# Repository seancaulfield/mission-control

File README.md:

# Mission Control: RAVE EDITION
### A nearly complete internal replacement for the IBM Model M122: Now with RGB!!

This project is designed to replace all internal compoents of an Model M122 keyboard, and is based off my previous [Mod Mmm Project](https://github.com/dcpedit/mod-mmm).  Only the curved steel backplate is needed for the PCB to be mounted on.

Image gallery: https://imgur.com/a/wuXMWVg

## Features

* Per-key RGB support
* High current 5V path (because we're going to be pulling a LOT of current...)
* FR4 plate files as alternative
* Hotswap sockets for MX switches
* Multiple layout support, including ISO, split spacebar, and 4x5 macropad for numpad. [KLE link](http://www.keyboard-layout-editor.com/#/gists/d71adbbb0de71b98bfe3e79a4a607b5c)
* PCB mount stabilizers
* Solenoid
* LCD display
* USB-C support
* Bluetooth support (via PillBug)
* QMK/VIA firmware
* ZMK firmware (for BT PillBug)

## The Build "Stack"

The following is a table of measurements of everything that's stacked on top of the steel backplate.  The key spacing was taken from hires scans I made of the Model M's wiring membrane.  I recalculated the spacing for each decrease in radius except for the foam where I reused the numbers from the switch plate.  I was lazy and figured foam can stretch anyways.

| Part            | Thickness (mm) | Radius (mm) | Radius Start | 1u vertical spacing (mm) |
|-----------------|----------------|-------------|--------------|--------------------------|
| Steel backplate | 1.0            | 276.635     | inner        | 20.617
| Hex Standoffs   | 4.0            | n/a         | n/a          | n/a
| PCB     | 1.0            | 272.135     | center       | 20.560
| Plate Foam      | 3.5            | n/a         | n/a          | n/a
| Switch Plate    | 1.5            | 267.385     | center       | 20.201

## Parts List

| Part                        | Count | Notes |
|-----------------------------|-------|-------|
| Mission Control PCB         | 1     | 1mm FR4 thickness
| Blackpill (STM32F411)       | 1     |
| M2.5x3mm Wafer Screw        | 138   | [Link](https://www.aliexpress.us/item/2255800885711092.html?spm=a2g0o.order_list.order_list_main.22.1875180223MOsy&gatewayAdapt=glo2usa&_randl_shipto=US)
| M2.5x4mm Hex Standoff       | 69    | [Link](https://www.aliexpress.us/item/2251832790997097.html?spm=a2g0o.order_list.order_list_main.23.1875180223MOsy&gatewayAdapt=glo2usa&_randl_shipto=US)
| BAV70 Diodoe                | 64    | [Link](https://www.mouser.com/ProductDetail/Nexperia/BAV70215?qs=me8TqzrmIYX%252B%2FJ6jIjzNeA%3D%3D&countrycode=US&currencycode=USD)
| Piezo Buzzer                | 1     | [Link](https://www.digikey.com/en/products/detail/tdk-corporation/PS1240P02BT/935924)
| 5v Solenoid                 | 1     | [Link](https://www.digikey.com/en/products/detail/sparkfun-electronics/ROB-11015/6163694)
| Hotswap Sockets       | 108 - 115 | Recommend Gateron v2
| 2mm LED                     | 2     | For switch status led. [Link](https://www.amazon.com/gp/product/B01C5HL0PO/ref=ppx_yo_dt_b_search_asin_title?ie=UTF8&th=1)
| 10kΩ Resistor               | 2     | For keycap LED. Smaller = brighter |
| 22kΩ Resistor               | 1     | Pullup for pin A10 |
| TIP120 Transistor           | 1     | For solenoid. [Link](https://www.amazon.com/gp/product/B08212F42Z/ref=ppx_yo_dt_b_search_asin_title?ie=UTF8&psc=1)
| 1N4001 Diode                | 1     | For solenoid. Comes with above kit |
| 2.2kΩ Resistor              | 1     | For solenoid. Comes with above kit |
| Mill-Max 315 sockets (1x20) | 2     |
| Mill-Max 315 sockets (1x4)  | 1     |
| Mill-Max round pin (¼in)    | 44    | [Link](https://www.mouser.com/ProductDetail/Mill-Max/3320-0-00-15-00-00-03-0?qs=s8Nb1z4Wn%2FQ16WBIwCPrTw%3D%3D&countryCode=US&currencyCode=USD)
| 2u plate mount stabilizer   | 7 - 10| Count varies based on layout
| 7u plate mount stabilizer   | 1     | For 7u spacebar
| Switch plate (5 piece set)  | 1     | Optional 1.5mm acrylic
| Switch plate (5 piece set)  | 1     | Optional 1mm FR4
| Case foam (under PCB)       | 1     | Optional 2mm EVA
| Plate Foam                  | 1     | Optional 3.5mm EVA foam (or 2mm + [1.5mm](https://www.aliexpress.us/item/3256804208838525.html?spm=a2g0o.order_list.order_list_main.5.21ef1802FA7EIC&gatewayAdapt=glo2usa&_randl_shipto=US))
| 2.2" ILI9341 display        | 1     | Optional display, [link](https://a.co/d/10fYStD)
| 8 pin headers (2.54mm pitch)| 2     | For optional display
| 8 pin ribbon cable          | 1     | For optional display
| USB-C panel mount           | 1     | [Link](https://a.aliexpress.com/_mLVMrx6)
| SK-6812E rev mount LEDs     | 122   | [Link](https://www.adafruit.com/product/4960)
| 3.5mm height M2.5 solderable standoffs | 76    | 
| 4mm height M2.5 M-F standoffs | 76    | 
| 4mm height M2.5 F-F standoffs | 32    | 
| 3mm M2.5 screws             | 184 |
| SN74LVC1G125DBV (SOT-23-5 non-inverting buffer) | 1 |
| 100n 0603 X5R capacitor     | 1 |

For the Mill-Max 315 series sockets, I found it more cost efficient to just buy a really long socket and cut the sizes I need with flush cutters.  [Here's an example of a 1x64 socket.](https://www.mouser.com/ProductDetail/Mill-Max/315-93-164-41-003000?qs=WZRMhwwaLl%252BIMh92Iwf2Uw%3D%3D&countryCode=US&).  Make sure to file down the rough edge after cutting.

## PCB Build Guild

To complete this build, you will need to get the main PCB manufactured with an **FR4 thickness of 1mm**.  I personally like using [JLCPCB](https://jlcpcb.com/), and I've included the gerber zip in the `pcb/production` folder.  (Note: you will need to order a minimum of 5 boards).

### 1) Disassembly
The first step is to disassemble your Model M and clean it if neccessary.  There are lots of tutorials online on how to do this, and make sure you have a 7/32 inch (5.5mm) socket for the case screws.

Remove the plastic rivets on the back of the steel plate with a pair of flush cutters.  Once this is done, all the components can be removed leaving just the steel plate.

### 2) Shape PCB

Using the hex standoffs and a few screws, mount the PCB onto the steel backplate for 24hrs.  You only need enough screws & standoffs for the PCB to hold its shape.  After you remove the PCB, you want there to be a slight curve to the FR4 before soldering on the components.  This way, the componenets and solder joints experience less stress when the PCB is bent into its final shape.

### 3) BAV70 Diodes

Flip the PCB over to the backside and solder on the BAV70 diodes (D1 - D64). Place a dab of solder on the single bottom pad of the diode on the PCB. Then using tweesers, position the diode so that the legs line up with the pads. Then using the point of one tweeser leg, gently hold the top of the diode in place while melting the dab of solder that was placed on the bottom pad previously. With the diode now held in position, solder the top two legs to their respective pads.

### 4) Hotswap Sockets

Place some solder on one of the hot swap socket pads. There should be enough solder to make a small mound. Place the socket into position and melt the mound of solder that was previously added while pressing down on the center of the socket. Be sure to avoid touching any metalic parts to prevent burns. Keep the soldering iron on the pad long enough for the solder to flow around the socket connector (usually around 3 to 4 seconds). Now solder the other socket connector to the pad.

### 5) 22k Pullup Resistor

In order to use pin A10 on the Blackpill, a 22k pullup resistor is needed (according to the [QMK docs](https://docs.qmk.fm/#/platformdev_blackpill_f4x1)). Solder this into the R3 position.  Orientation does not matter.

### 6) Blackpill Development Board

It's probably best to flash the firmware onto the Blackpill first using the `bin` file in the `firmware` directory. Hook it up to [QMK Toolbox](https://github.com/qmk/qmk_toolbox/releases) and push the following buttons to place it in bootloader mode before flashing:
* Press and hold the BOOT0 button
* Press and release NRST (reset) button
* Release BOOT0 button

Solder the Mill-Max 315 sockets onto the daughterboard.  Then place a piece of masking tape over the pin holes, and insert each pin though the tape and into its hole with tweezers.  Then set the Blackpill into place with the components facing up and the USB port facing the top of the daughterboard.  Solder the pins into place, and then carefully and slowly remove the Blackpill.  If you pull too fast and hard, one edge will suddenly pop loose, bending the pins on the opposite side.  Remove the masking tape, and push the Blackpill back into place.

Lazy-man's short cut: skip the masking tape.  But note that using too much solder will cause it to flow down the pin and into the socket.  If this happens, the keyboard will still work, but you won't be able to remove the Blackpill without desoldering.

## Choose build option

At this point in the build, you will need to choose between ONE of the following 2 options.

### Option #1: Solenoid, buzzer, and status LEDs

#### a) Solenoid Components
Bend the narrow part of the pins on the TIP120 back towards the heatsink at a 90 degree angle.  Solder it into the TIP1 position.

The 2.2k resistor goes into the R4 spot (orientation does not matter).  The 1N4001 diode goes in to the 1N1 position where the line matches the printed line on the board.  The solenoid wires don't have an orientation, and you can solder them directly into the holes or use a header/connector.

#### b) Piezo Buzzer

Solder this into the BZ1 position.  Orientation does not matter.

#### c) Switch LEDs and resistors (optional)

These LEDs go under the caps lock and scroll lock switches.  Depending on your switch, you may have to solder these in AFTER placing the switch into the socket.  You can tell by looking under the switch to see if there's a hole big enough for the LED to fit through.  If there are only 2 small holes for the LED pins, then the switch needs to go in first.  The short pin of the LED goes in the square pad.  As for the accompanying 10kΩ resistors (R1 and R2), orientation does not matter.

I use a higher resistance here for the white LEDs because they tend to be too bright for me personally.  Feel free to lower the resistance if you want them brighter, or if you choose a different color.

### Option #2: LCD display

#### a) Display headers

Mount headers for on the PCB facing down (PCB position J1) and right angled headers on the display facing towards the right

#### b) Cut display window

Turn on your display, and measure the physical height and width of the display area.  This will be the size of your case "window".  Use masking tape to mark the edges of the window on the top of your case and cut the hole out.

I believe the best tool for this job is with a CNC router.  Since I didn't have access to one, I first used a dremel with a cutting disk to cut the hole out.  Then I smoothed the edges with a file, and then with fine grit sand sand paper wrapped around a flat piece of plastic.  I found that adding a chamfered edge makes it look more "finished".

#### c) Mounting display

I found that the easiest thing to do here is to first connect the display to the PCB with the ribbon cable and power it up.  Center the displayed image within the window, and while holding it firmly in place, place hot glue in each corner of the display's PCB, allowing some to flow through the mounting holes.

## Continue with main build

### 7) Stabilizers

Install your stabilizers of choice onto the PCB.  For the vertical stabs, in order to counteract the curvature of the PCB, I used adhesive stabilizer pads and cut them in half lengthwise (band-aids would work as well).  I then placed them on the inside half of where the stabs would sit.  The idea here is to angle the stabs back outwards so that they remain parallel.

Note that I made all the stab holes a tad larger in the vertical direction to allow for some wiggle room.

### 8) Install PCB standoffs

Starting with the steel backplate, insert a screw from the back and screw a standoff on from the other side.  Keep it loose enough so that the standoff can rattle around a bit.  Do this for all the mount holes on the steel plate, even if you end up not using them because they're still good for support.  Omit any standoff that interferes with your stabilizers.

Slip the steel backplate back into the bottom of the case.  You'll need to slide the bottom into the slots first, and then place the plastic case posts into the top-left and top-right corners of the steel backplate.

### 9) Case foam (optional)

If you opted for the 2mm EVA case foam, you'll need to place it over the steel plate before installing the PCB.  The holes in the foam should line up over the standoffs. (Filename: `case/case-foam.ai`)

### 10) Center and Install PCB

Line up the PCB over the holes and place 2 or 3 screws positioned horizontally from each other near the center of the PCB.  Push the center firmly down onto the standoffs to force the PCB to bend (this part is a bit nerve racking, especialy when you hear creaking noises), and secure it with the screws while holding it in place.

Shift the steel backplate all the way to the top until it can't move anymore.  This is the correct position of the plate, so I'd recommend wedging strips of 2mm foam between the case the bottom edge of the case.

Now place a switch and keycap combo at the corner of every section of the keyboard.  Put the top of the case on, making sure it's aligned and fully seated with no gaps.  Carefully shift the PCB around slightly to get the keycaps to be in the correct position with equal amounts of spacing from the keycap to the case walls.  Basically you're trying to center the PCB by eye-balling the keycap gaps.

With the PCB now centered, remove the top of the case and begin screwing in all the mounting screws.  I'd suggest starting near the center and spiral outwards towards the edges.  This is where you'll probably need to shift the loose standoffs around to line the holes up.  Also, if you run into the problem where the top and bottom screws bump into each other inside the standoff, you'll need to add an insulated washer to the bottom screw.  Place the top case back on every once in a while to make sure the PCB didn't shift and is still centered.  After you're done, remove the steel backplate from the bottom of the case and tighten all the screws on the back.  If you feel that the standoffs are just spinning while you're turning the screw, just squeeze the PCB and backplate together so that it pinches the standoff and keeps it from spinning.

## Assembly photos

## Firmware

Binaries are located in the `firmware` directory.

Source code is located in the `missioncontrol` branch of my QMK fork:

https://github.com/dcpedit/qmk_firmware/tree/mission-control/keyboards/dcpedit/missioncontrol

The LCD build requires it's own separate firmware because it uses the solenoid/buzz/LED pins.

### Change graphic

Copy your 240x320 image (320x240 image rotated counter-clockwise 90 degrees) into the following QMK directory:

```
keyboards/dcpedit/missioncontrol/lcd/image/background.png
```

Then run the following command from that directory

```
qmk painter-convert-graphics -f rgb565 -i background.png -o ./
```

That will generate a new `*.c` and `*.h` file.  You can now compile the firmware:

```
make dcpedit/missioncontrol/lcd:via
```

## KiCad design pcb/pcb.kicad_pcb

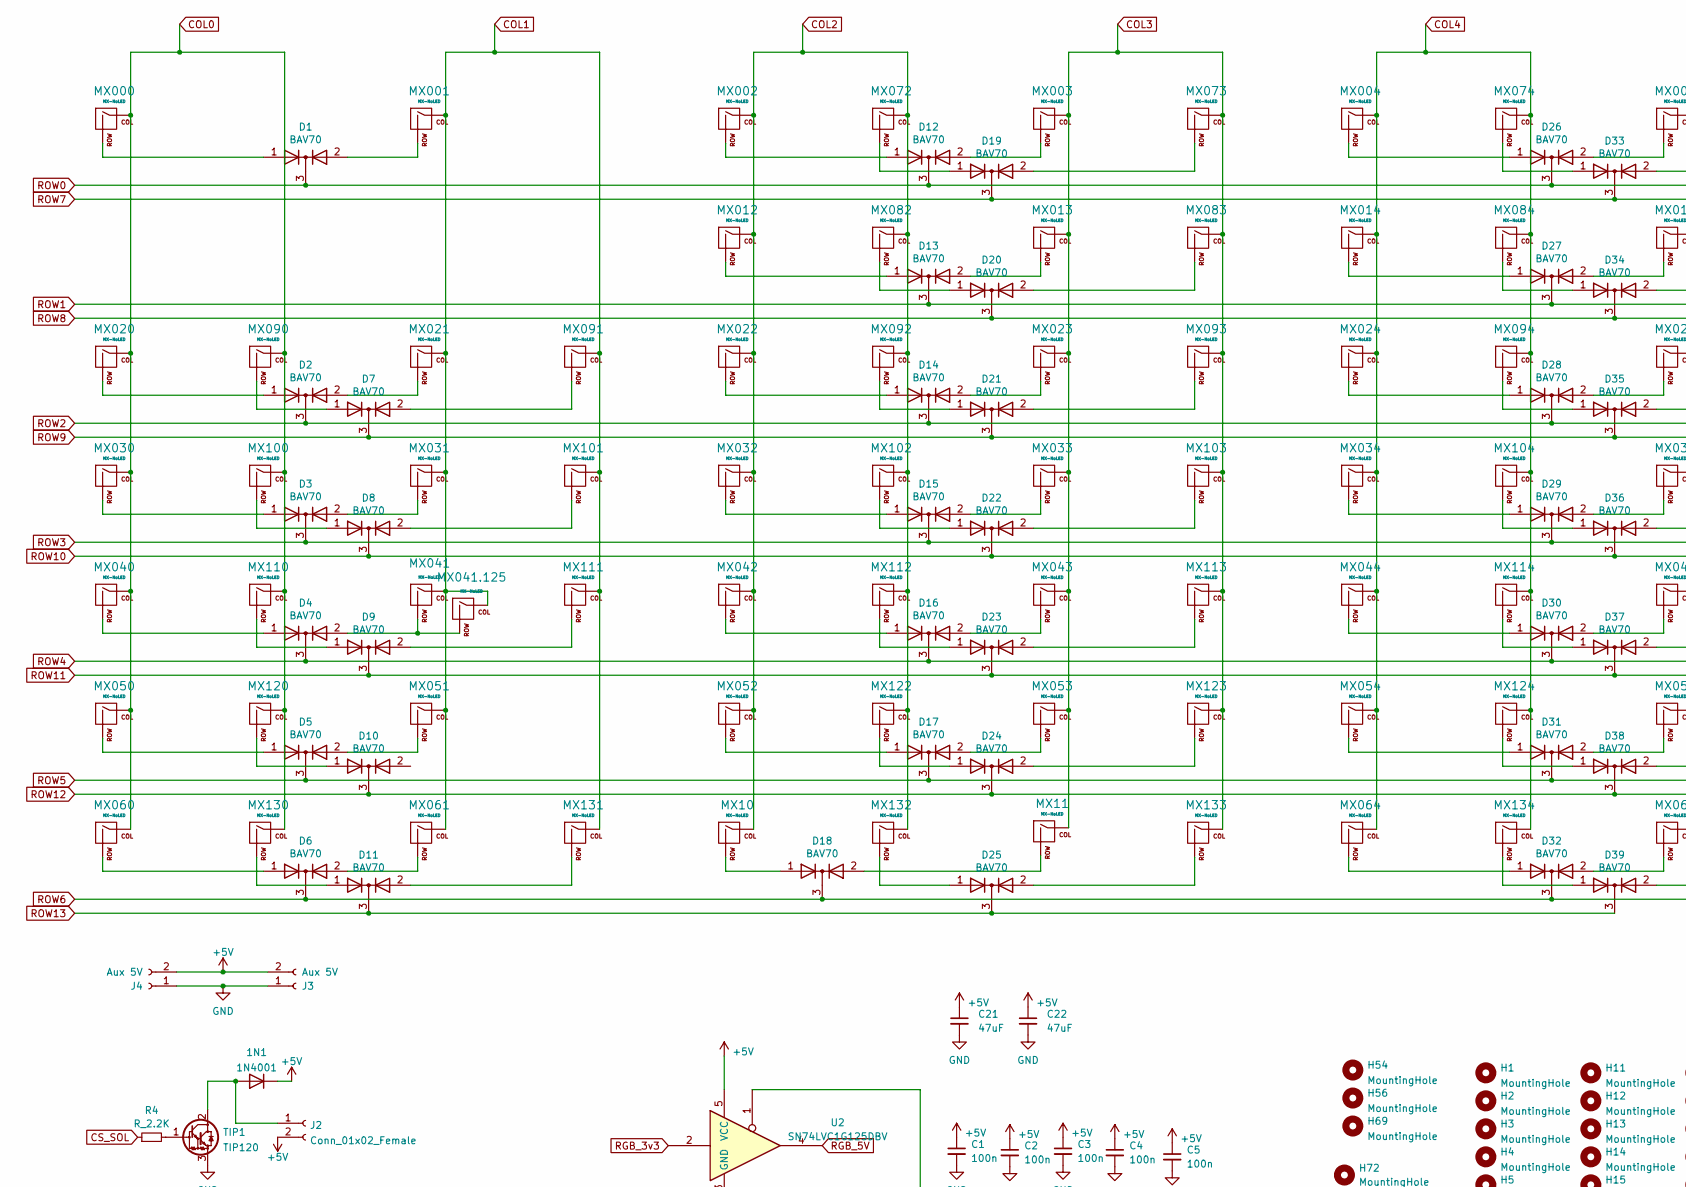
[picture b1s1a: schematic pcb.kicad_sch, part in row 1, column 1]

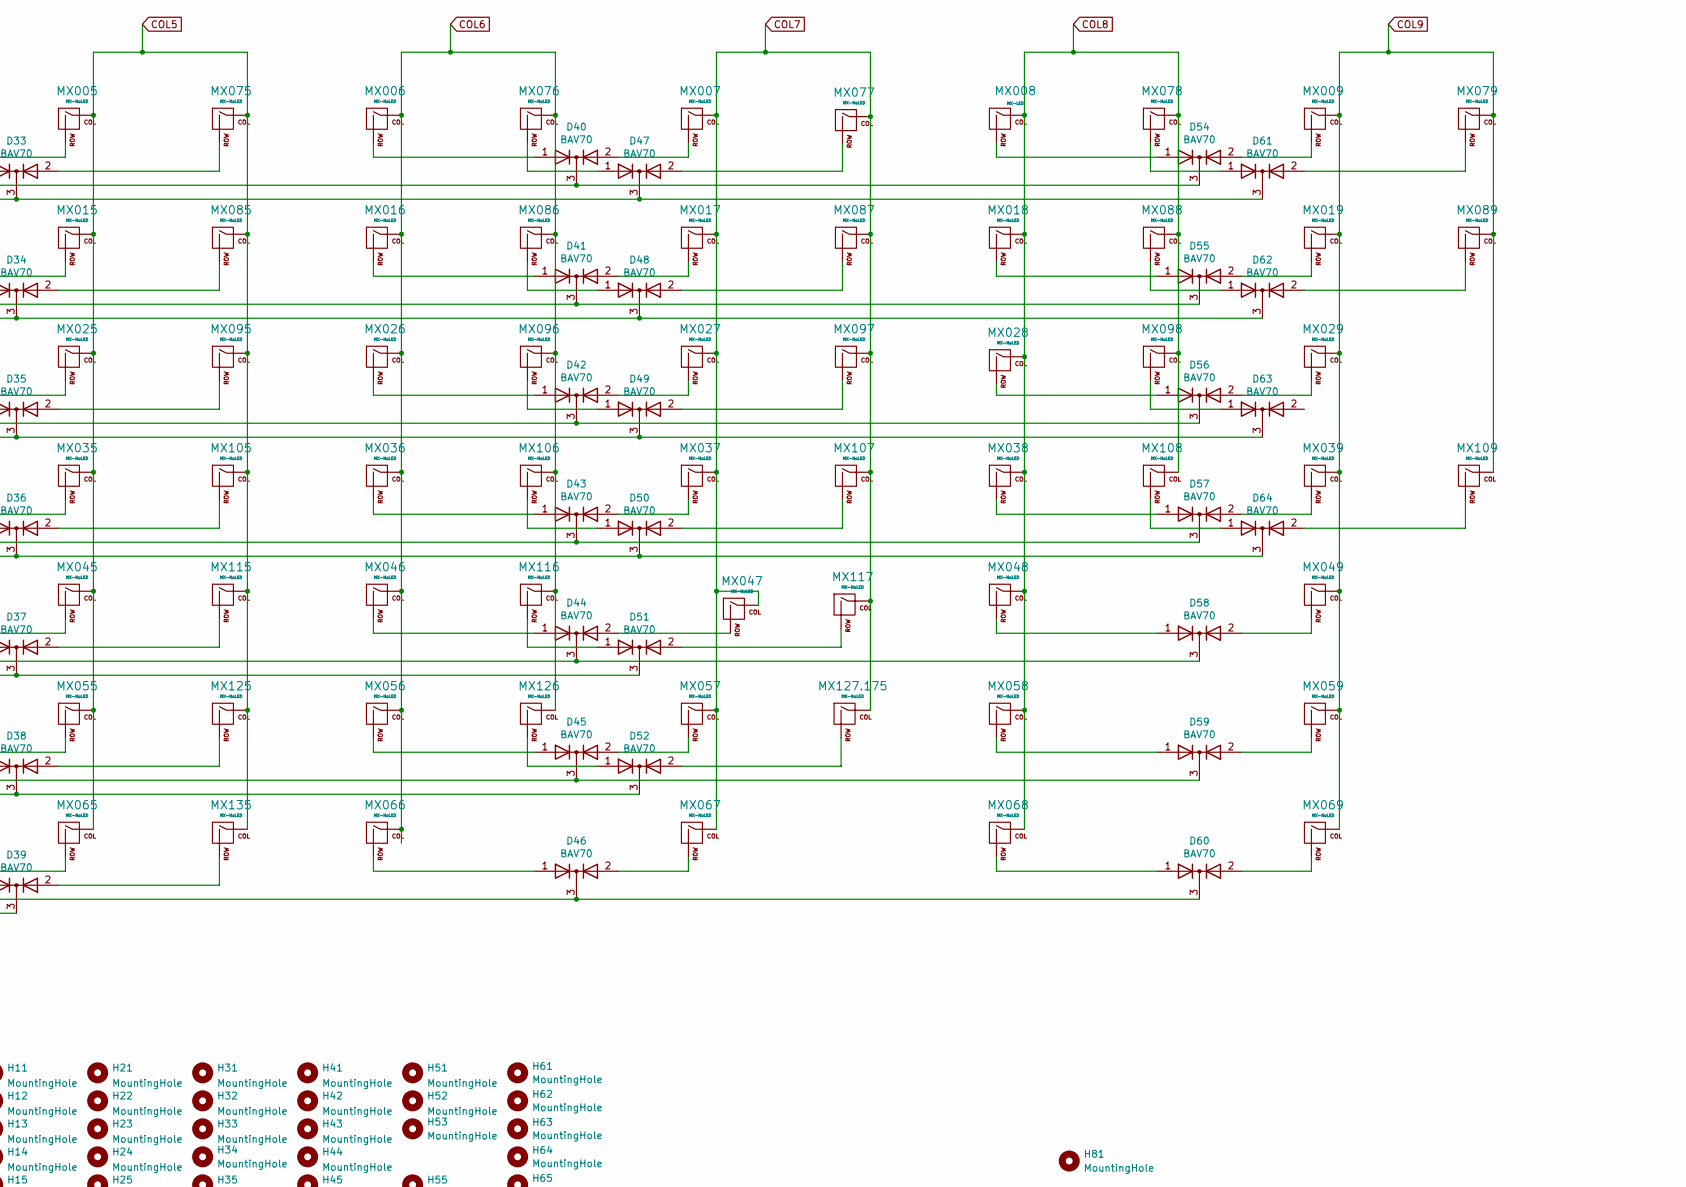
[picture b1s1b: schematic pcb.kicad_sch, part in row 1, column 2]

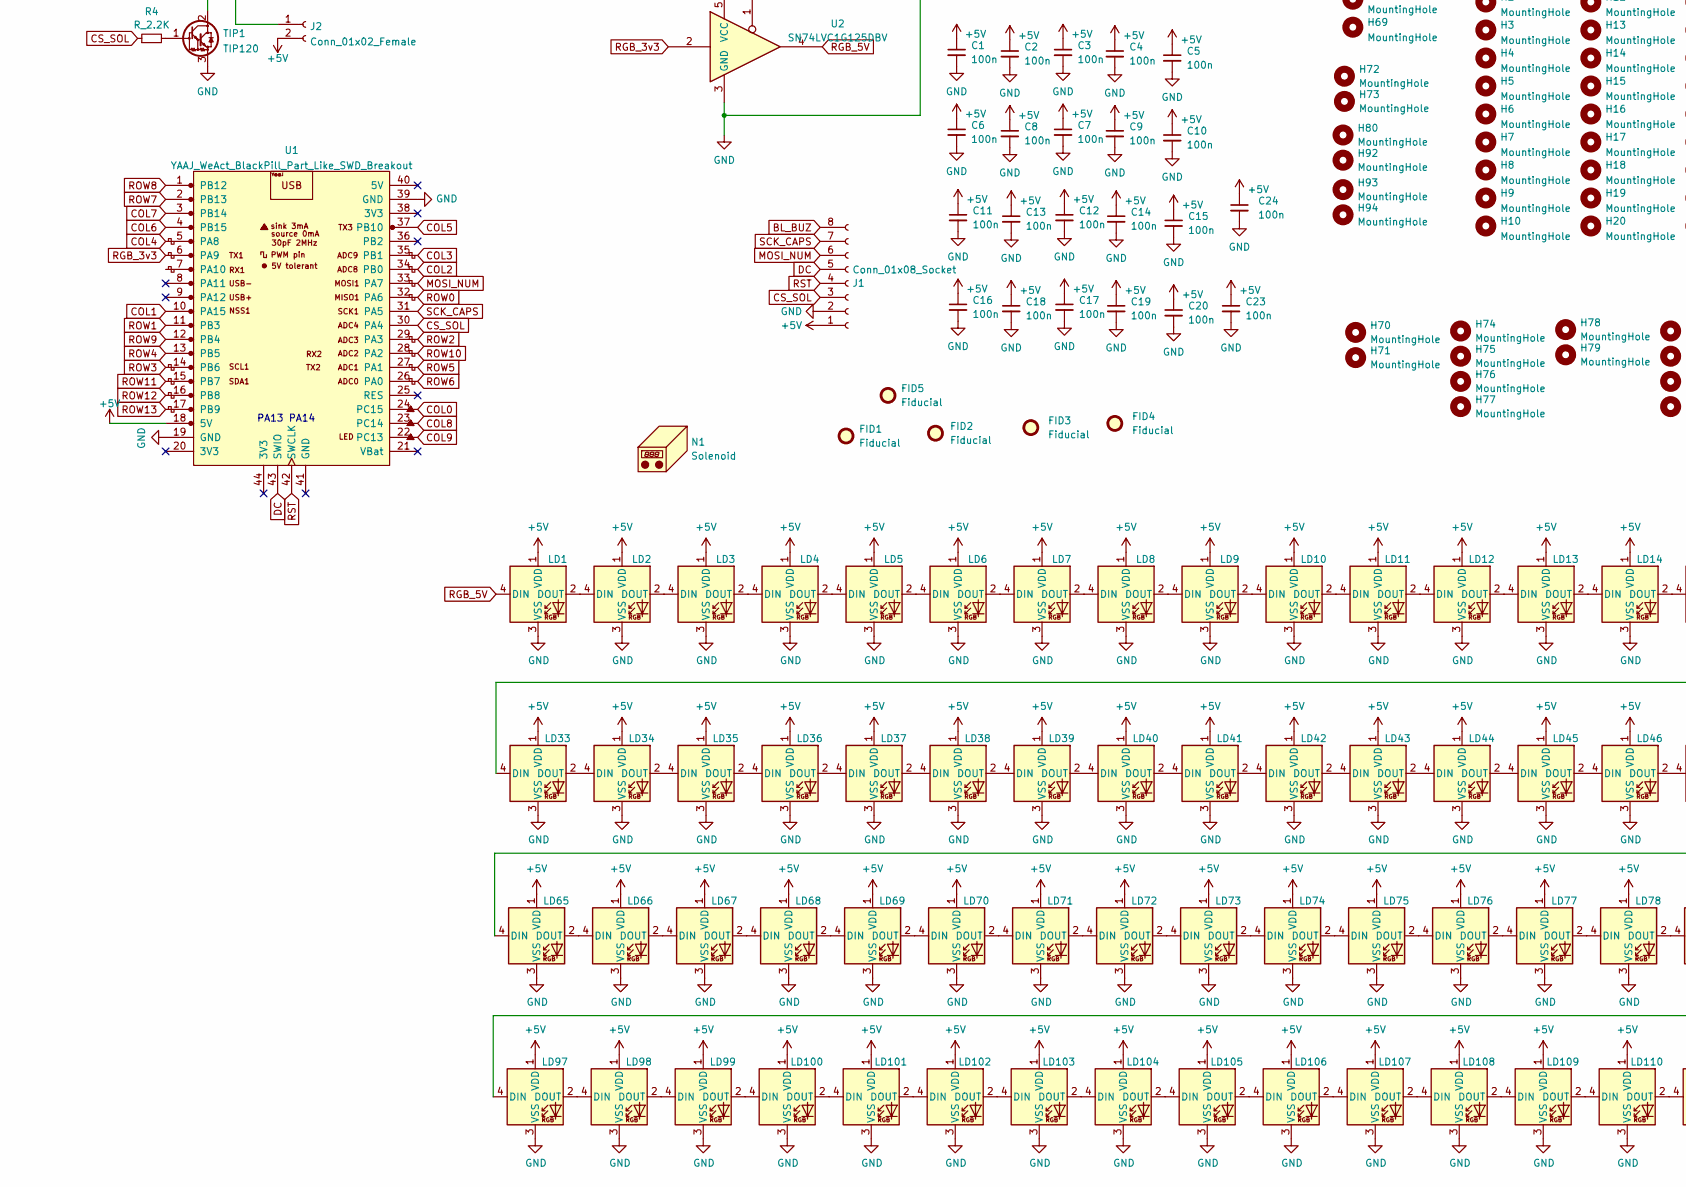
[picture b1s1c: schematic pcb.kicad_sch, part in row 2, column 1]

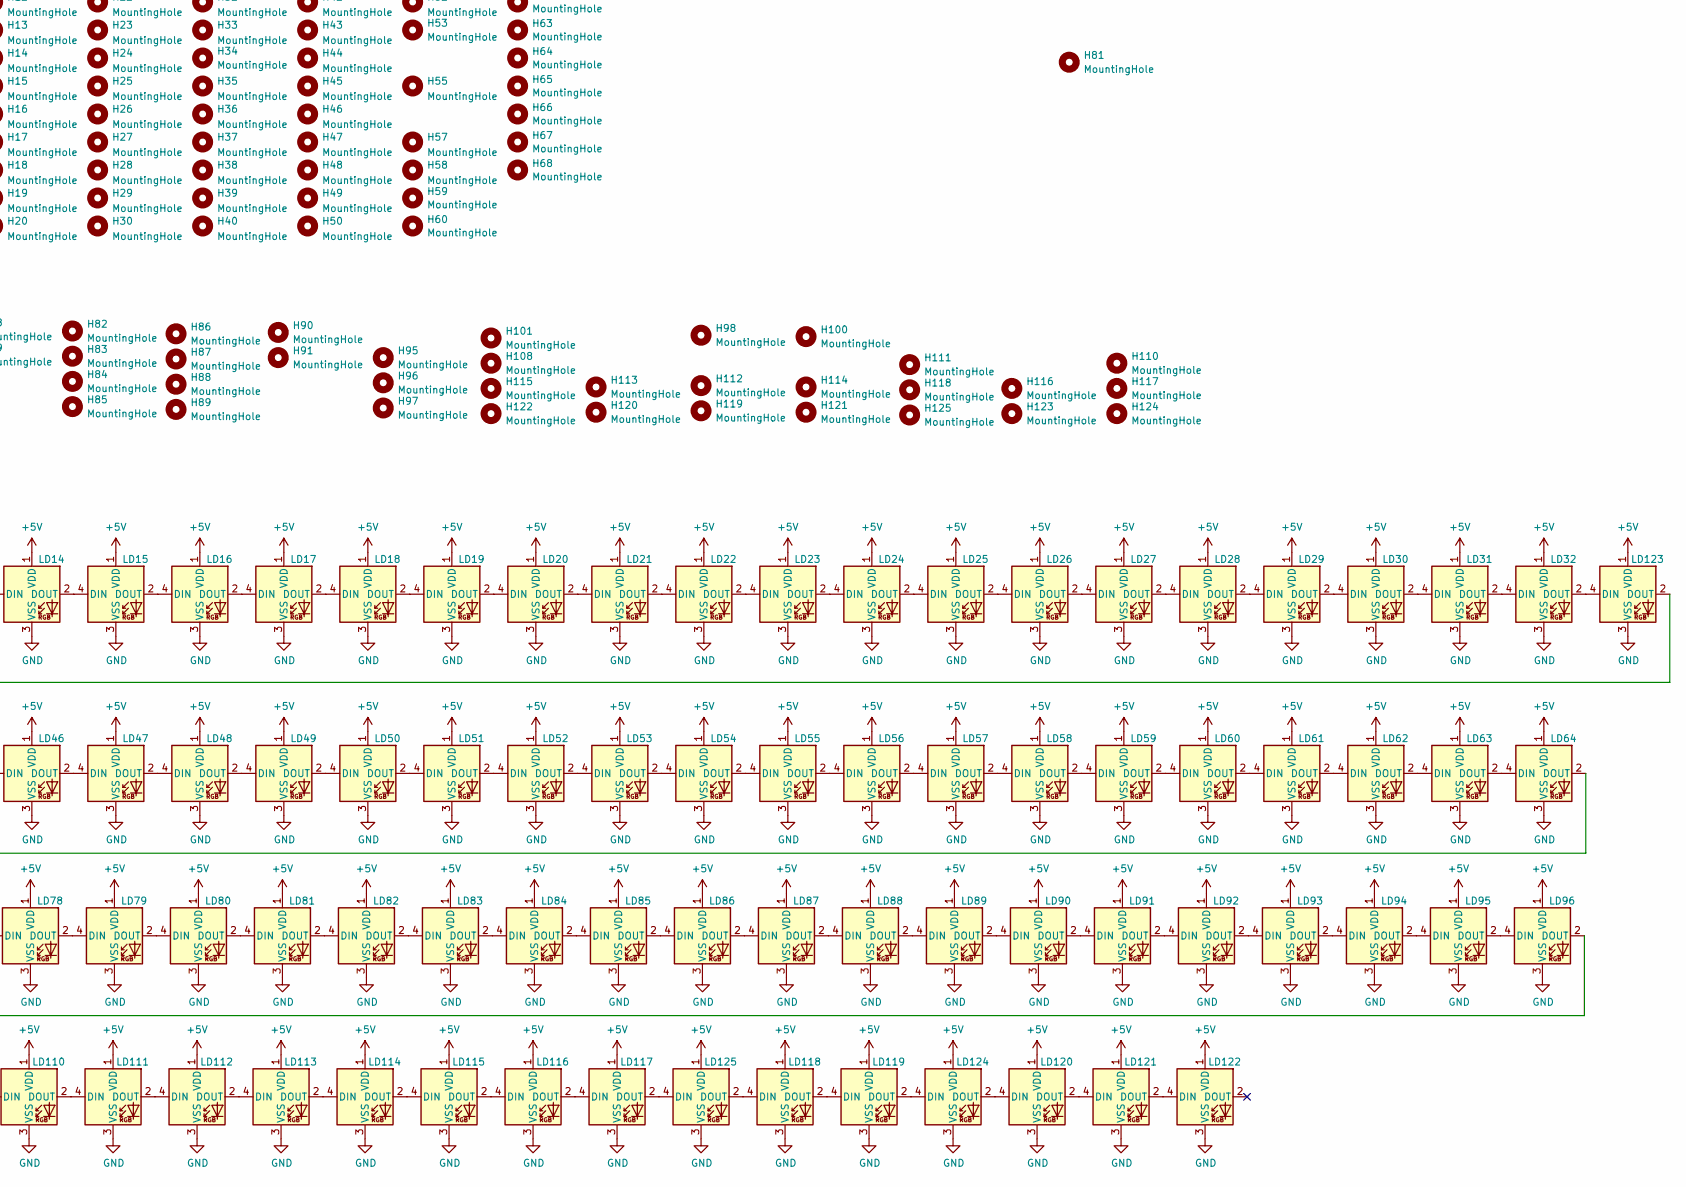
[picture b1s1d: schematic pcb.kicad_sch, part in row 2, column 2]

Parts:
1N1: 1N4001; D_DO-41_SOD81_P10.16mm_Horizontal
C1, C2, C3, C4, C5, C6, C7, C8, C9, C10, C11, C12, C13, C14, C15, C16, C17, C18, C19, C20, C23: 100n; C_0603_1608Metric
C21, C22: 47uF; CP_Radial_D10.0mm_P2.50mm_P5.00mm
C24: 100n; C_0805_2012Metric
D1, D2, D3, D4, D5, D6, D7, D8, D9, D10, D11, D12, D13, D14, D15, D16, D17, D18, D19, D20, D21, D22, D23, D24, D25, D26, D27, D28, D29, D30, D31, D32, D33, D34, D35, D36, D37, D38, D39, D40, D41, D42, D43, D44, D45, D46, D47, D48, D49, D50, D51, D52, D54, D55, D56, D57, D58, D59, D60, D61, D62, D63, D64: BAV70; SOT-23_Handsoldering
FID1, FID5: Fiducial; COW
FID2: Fiducial; oshw
FID3, FID4: Fiducial; qmk_logo
H1, H6, H7, H11, H12, H13, H14, H15, H16, H43, H51, H60, H61, H62, H63, H64, H65, H66, H67, H68, H70, H71, H85, H86, H88, H92, H93, H94, H120, H121, H122, H123, H125: MountingHole; MountingHole_3.0mm_M2_5mm_dia_solderable
H2, H3, H4, H5, H8, H9, H10, H17, H18, H19, H20, H21, H22, H23, H24, H25, H26, H27, H28, H29, H30, H31, H32, H33, H34, H35, H36, H37, H38, H39, H40, H41, H42, H44, H45, H46, H47, H48, H49, H50, H52, H53, H54, H55, H56, H57, H58, H59, H69, H72, H73, H74, H75, H76, H77, H78, H79, H80, H81, H82, H83, H84, H87, H89, H90, H91, H95, H96, H97, H98, H100, H101, H108, H110, H111, H112, H113, H114, H115, H116, H117, H118, H119, H124: MountingHole; MountingHole_2.6mm_M2_4mm_dia_solderable_tighter_hole
J1: Conn_01x08_Socket; PinHeader_1x08_P2.54mm_Vertical
J2: Conn_01x02_Female; PinHeader_1x02_P2.54mm_Vertical
J3: Aux 5V; TerminalBlock_bornier-2_P5.08mm
J4: Aux 5V; SolderWire-2sqmm_1x02_P7.8mm_D2mm_OD3.9mm
LD1, LD2, LD3, LD4, LD5, LD6, LD7, LD8, LD9, LD10, LD11, LD12, LD13, LD14, LD15, LD16, LD17, LD18, LD19, LD20, LD21, LD22, LD23, LD24, LD25, LD26, LD27, LD28, LD29, LD30, LD31, LD32, LD33, LD34, LD35, LD36, LD37, LD38, LD39, LD40, LD41, LD42, LD43, LD44, LD45, LD46, LD47, LD48, LD49, LD50, LD51, LD52, LD53, LD54, LD55, LD56, LD57, LD58, LD59, LD60, LD61, LD62, LD63, LD64, LD65, LD66, LD67, LD68, LD69, LD70, LD71, LD72, LD73, LD74, LD75, LD76, LD77, LD78, LD79, LD80, LD81, LD82, LD83, LD84, LD85, LD86, LD87, LD88, LD89, LD90, LD91, LD92, LD93, LD94, LD95, LD96, LD97, LD98, LD99, LD100, LD101, LD102, LD103, LD104, LD105, LD106, LD107, LD108, LD109, LD110, LD111, LD112, LD113, LD114, LD115, LD116, LD117, LD118, LD119, LD120, LD121, LD122, LD123, LD124, LD125: WS2812B; LED_SK6812MINI_PLCC4_3.1x2.7mm_P1.75mm_reverse_mount
MX000, MX001, MX002, MX003, MX004, MX005, MX006, MX007, MX009, MX10, MX11, MX012, MX013, MX014, MX015, MX016, MX017, MX018, MX019, MX020, MX021, MX022, MX023, MX024, MX025, MX026, MX027, MX028, MX029, MX030, MX032, MX033, MX034, MX035, MX036, MX037, MX038, MX039, MX040, MX042, MX043, MX044, MX045, MX046, MX048, MX049, MX050, MX052, MX053, MX054, MX055, MX056, MX057, MX058, MX059, MX060, MX065, MX067, MX068, MX069, MX072, MX073, MX074, MX075, MX076, MX077, MX078, MX079, MX082, MX083, MX084, MX085, MX086, MX087, MX088, MX090, MX091, MX092, MX093, MX094, MX095, MX096, MX097, MX098, MX100, MX101, MX102, MX103, MX104, MX105, MX106, MX107, MX108, MX110, MX111, MX112, MX113, MX114, MX115, MX116, MX120, MX122, MX123, MX124, MX125, MX126, MX130, MX131, MX133, MX134, MX135: MX-NoLED; MXOnly-1U-Hotswap
MX008: MX-LED; MXOnly-1U-Hotswap
MX031, MX061, MX064, MX117: MX-NoLED; MXOnly-1.5U-Hotswap
MX041, MX127.175: MX-NoLED; MXOnly-1.75U-Hotswap
MX041.125: MX-NoLED; MXOnly-1.25U-Hotswap
MX047: MX-NoLED; MXOnly-2.25U-Hotswap-ReversedStabilizers
MX051: MX-NoLED; MXOnly-2.25U-Hotswap
MX066: MX-NoLED; MXOnly-2U-Hotswap
MX089, MX109: MX-NoLED; MXOnly-2U-Hotswap-ReversedVerticalStabilizers
MX132: MX-NoLED; MXOnly-6U-Centered-Hotswap
N1: Solenoid; solenoid
R4: R_2.2K; Resistor-Hybrid
TIP1: TIP120; TO-220-3_Vertical
U1: YAAJ_WeAct_BlackPill_Part_Like_SWD_Breakout; YAAJ_WeAct_BlackPill_SWD_2
U2: SN74LVC1G125DBV; SOT-23-5

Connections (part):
+5V: 1N1.1 (K), C1.1, C2.1, C3.1, C4.1, C5.1, C6.1, C7.1, C8.1, C9.1, C10.1, C11.1, C12.1, C13.1, C14.1, C15.1, C16.1, C17.1, C18.1, C19.1, C20.1, C21.1, C22.1, C23.1, C24.1, J1.1, J2.2, J3.2, J4.2, LD1.1 (VDD), LD2.1 (VDD), LD3.1 (VDD), LD4.1 (VDD), LD5.1 (VDD), LD6.1 (VDD), LD7.1 (VDD), LD8.1 (VDD), LD9.1 (VDD), LD10.1 (VDD), LD11.1 (VDD), LD12.1 (VDD), LD13.1 (VDD), LD14.1 (VDD), LD15.1 (VDD), LD16.1 (VDD), LD17.1 (VDD), LD18.1 (VDD), LD19.1 (VDD), LD20.1 (VDD), LD21.1 (VDD), LD22.1 (VDD), LD23.1 (VDD), LD24.1 (VDD), LD25.1 (VDD), LD26.1 (VDD), LD27.1 (VDD), LD28.1 (VDD), LD29.1 (VDD), LD30.1 (VDD), LD31.1 (VDD), LD32.1 (VDD), LD33.1 (VDD), LD34.1 (VDD), LD35.1 (VDD), LD36.1 (VDD), LD37.1 (VDD), LD38.1 (VDD), LD39.1 (VDD), LD40.1 (VDD), LD41.1 (VDD), LD42.1 (VDD), LD43.1 (VDD), LD44.1 (VDD), LD45.1 (VDD), LD46.1 (VDD), LD47.1 (VDD), LD48.1 (VDD), LD49.1 (VDD), LD50.1 (VDD), LD51.1 (VDD), LD52.1 (VDD)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
BL_BUZ: J1.8
COL0: MX000.1 (COL), MX020.1 (COL), MX030.1 (COL), MX040.1 (COL), MX050.1 (COL), MX060.1 (COL), MX090.1 (COL), MX100.1 (COL), MX110.1 (COL), MX120.1 (COL), MX130.1 (COL), U1.24 (PC15)
COL1: MX001.1 (COL), MX021.1 (COL), MX031.1 (COL), MX041.1 (COL), MX041.125.1 (COL), MX051.1 (COL), MX061.1 (COL), MX091.1 (COL), MX101.1 (COL), MX111.1 (COL), MX131.1 (COL), U1.10 (PA15)
COL2: MX002.1 (COL), MX10.1 (COL), MX012.1 (COL), MX022.1 (COL), MX032.1 (COL), MX042.1 (COL), MX052.1 (COL), MX072.1 (COL), MX082.1 (COL), MX092.1 (COL), MX102.1 (COL), MX112.1 (COL), MX122.1 (COL), MX132.1 (COL), U1.34 (PB0)
COL3: MX003.1 (COL), MX11.1 (COL), MX013.1 (COL), MX023.1 (COL), MX033.1 (COL), MX043.1 (COL), MX053.1 (COL), MX073.1 (COL), MX083.1 (COL), MX093.1 (COL), MX103.1 (COL), MX113.1 (COL), MX123.1 (COL), MX133.1 (COL), U1.35 (PB1)
COL4: MX004.1 (COL), MX014.1 (COL), MX024.1 (COL), MX034.1 (COL), MX044.1 (COL), MX054.1 (COL), MX064.1 (COL), MX074.1 (COL), MX084.1 (COL), MX094.1 (COL), MX104.1 (COL), MX114.1 (COL), MX124.1 (COL), MX134.1 (COL), U1.5 (PA8)
COL5: MX005.1 (COL), MX015.1 (COL), MX025.1 (COL), MX035.1 (COL), MX045.1 (COL), MX055.1 (COL), MX065.1 (COL), MX075.1 (COL), MX085.1 (COL), MX095.1 (COL), MX105.1 (COL), MX115.1 (COL), MX125.1 (COL), MX135.1 (COL), U1.37 (PB10)
COL6: MX006.1 (COL), MX016.1 (COL), MX026.1 (COL), MX036.1 (COL), MX046.1 (COL), MX056.1 (COL), MX066.1 (COL), MX076.1 (COL), MX086.1 (COL), MX096.1 (COL), MX106.1 (COL), MX116.1 (COL), MX126.1 (COL), U1.4 (PB15)
COL7: MX007.1 (COL), MX017.1 (COL), MX027.1 (COL), MX037.1 (COL), MX047.1 (COL), MX057.1 (COL), MX067.1 (COL), MX077.1 (COL), MX087.1 (COL), MX097.1 (COL), MX107.1 (COL), MX117.1 (COL), MX127.175.1 (COL), U1.3 (PB14)
COL8: MX008.1 (COL), MX018.1 (COL), MX028.1 (COL), MX038.1 (COL), MX048.1 (COL), MX058.1 (COL), MX068.1 (COL), MX078.1 (COL), MX088.1 (COL), MX098.1 (COL), MX108.1 (COL), U1.23 (PC14)
COL9: MX009.1 (COL), MX019.1 (COL), MX029.1 (COL), MX039.1 (COL), MX049.1 (COL), MX059.1 (COL), MX069.1 (COL), MX079.1 (COL), MX089.1 (COL), MX109.1 (COL), U1.22 (PC13)
CS_SOL: J1.3, R4.1, U1.30 (PA4)
DC: J1.5, U1.43 (SWIO)
GND: C1.2, C2.2, C3.2, C4.2, C5.2, C6.2, C7.2, C8.2, C9.2, C10.2, C11.2, C12.2, C13.2, C14.2, C15.2, C16.2, C17.2, C18.2, C19.2, C20.2, C21.2, C22.2, C23.2, C24.2, J1.2, J3.1, J4.1, LD1.3 (VSS), LD2.3 (VSS), LD3.3 (VSS), LD4.3 (VSS), LD5.3 (VSS), LD6.3 (VSS), LD7.3 (VSS), LD8.3 (VSS), LD9.3 (VSS), LD10.3 (VSS), LD11.3 (VSS), LD12.3 (VSS), LD13.3 (VSS), LD14.3 (VSS), LD15.3 (VSS), LD16.3 (VSS), LD17.3 (VSS), LD18.3 (VSS), LD19.3 (VSS), LD20.3 (VSS), LD21.3 (VSS), LD22.3 (VSS), LD23.3 (VSS), LD24.3 (VSS), LD25.3 (VSS), LD26.3 (VSS), LD27.3 (VSS), LD28.3 (VSS), LD29.3 (VSS), LD30.3 (VSS), LD31.3 (VSS), LD32.3 (VSS), LD33.3 (VSS), LD34.3 (VSS), LD35.3 (VSS), LD36.3 (VSS), LD37.3 (VSS), LD38.3 (VSS), LD39.3 (VSS), LD40.3 (VSS), LD41.3 (VSS), LD42.3 (VSS), LD43.3 (VSS), LD44.3 (VSS), LD45.3 (VSS), LD46.3 (VSS), LD47.3 (VSS), LD48.3 (VSS), LD49.3 (VSS), LD50.3 (VSS), LD51.3 (VSS), LD52.3 (VSS), LD53.3 (VSS), LD54.3 (VSS)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
MOSI_NUM: J1.6, U1.33 (PA7)
unnamed: 1N1.2 (A), J2.1, TIP1.2 (C)
unnamed: LD1.2 (DOUT), LD2.4 (DIN)
unnamed: LD2.2 (DOUT), LD3.4 (DIN)
unnamed: LD3.2 (DOUT), LD4.4 (DIN)
unnamed: LD4.2 (DOUT), LD5.4 (DIN)
unnamed: LD5.2 (DOUT), LD6.4 (DIN)
unnamed: LD6.2 (DOUT), LD7.4 (DIN)
unnamed: LD7.2 (DOUT), LD8.4 (DIN)
unnamed: LD8.2 (DOUT), LD9.4 (DIN)
unnamed: LD9.2 (DOUT), LD10.4 (DIN)
unnamed: LD10.2 (DOUT), LD11.4 (DIN)
unnamed: LD11.2 (DOUT), LD12.4 (DIN)
unnamed: LD12.2 (DOUT), LD13.4 (DIN)
unnamed: LD13.2 (DOUT), LD14.4 (DIN)
unnamed: LD14.2 (DOUT), LD15.4 (DIN)
unnamed: LD15.2 (DOUT), LD16.4 (DIN)
unnamed: LD16.2 (DOUT), LD17.4 (DIN)
unnamed: LD17.2 (DOUT), LD18.4 (DIN)
unnamed: LD18.2 (DOUT), LD19.4 (DIN)
unnamed: LD19.2 (DOUT), LD20.4 (DIN)
unnamed: LD20.2 (DOUT), LD21.4 (DIN)
unnamed: LD21.2 (DOUT), LD22.4 (DIN)
unnamed: LD22.2 (DOUT), LD23.4 (DIN)
unnamed: LD23.2 (DOUT), LD24.4 (DIN)
unnamed: LD24.2 (DOUT), LD25.4 (DIN)
unnamed: LD25.2 (DOUT), LD26.4 (DIN)
unnamed: LD26.2 (DOUT), LD27.4 (DIN)
unnamed: LD27.2 (DOUT), LD28.4 (DIN)
unnamed: LD28.2 (DOUT), LD29.4 (DIN)
unnamed: LD29.2 (DOUT), LD30.4 (DIN)
unnamed: LD30.2 (DOUT), LD31.4 (DIN)
unnamed: LD31.2 (DOUT), LD32.4 (DIN)
unnamed: LD33.2 (DOUT), LD34.4 (DIN)
unnamed: LD34.2 (DOUT), LD35.4 (DIN)
unnamed: LD35.2 (DOUT), LD36.4 (DIN)
unnamed: LD36.2 (DOUT), LD37.4 (DIN)
unnamed: LD37.2 (DOUT), LD38.4 (DIN)
unnamed: LD38.2 (DOUT), LD39.4 (DIN)
unnamed: LD39.2 (DOUT), LD40.4 (DIN)
unnamed: LD40.2 (DOUT), LD41.4 (DIN)
unnamed: LD41.2 (DOUT), LD42.4 (DIN)
unnamed: LD42.2 (DOUT), LD43.4 (DIN)
unnamed: LD43.2 (DOUT), LD44.4 (DIN)
unnamed: LD44.2 (DOUT), LD45.4 (DIN)
unnamed: LD45.2 (DOUT), LD46.4 (DIN)
unnamed: LD46.2 (DOUT), LD47.4 (DIN)
unnamed: LD47.2 (DOUT), LD48.4 (DIN)
unnamed: LD48.2 (DOUT), LD49.4 (DIN)
unnamed: LD49.2 (DOUT), LD50.4 (DIN)
unnamed: LD50.2 (DOUT), LD51.4 (DIN)
unnamed: LD51.2 (DOUT), LD52.4 (DIN)
unnamed: LD52.2 (DOUT), LD53.4 (DIN)
unnamed: LD53.2 (DOUT), LD54.4 (DIN)
unnamed: LD54.2 (DOUT), LD55.4 (DIN)
unnamed: LD55.2 (DOUT), LD56.4 (DIN)
unnamed: LD56.2 (DOUT), LD57.4 (DIN)
unnamed: LD57.2 (DOUT), LD58.4 (DIN)
unnamed: LD58.2 (DOUT), LD59.4 (DIN)
unnamed: LD59.2 (DOUT), LD60.4 (DIN)
unnamed: LD60.2 (DOUT), LD61.4 (DIN)
unnamed: LD61.2 (DOUT), LD62.4 (DIN)
unnamed: LD62.2 (DOUT), LD63.4 (DIN)
unnamed: LD63.2 (DOUT), LD64.4 (DIN)
unnamed: LD64.2 (DOUT), LD65.4 (DIN)
unnamed: LD65.2 (DOUT), LD66.4 (DIN)
unnamed: LD66.2 (DOUT), LD67.4 (DIN)
unnamed: LD67.2 (DOUT), LD68.4 (DIN)
unnamed: LD68.2 (DOUT), LD69.4 (DIN)
unnamed: LD69.2 (DOUT), LD70.4 (DIN)
unnamed: LD70.2 (DOUT), LD71.4 (DIN)
unnamed: LD71.2 (DOUT), LD72.4 (DIN)
unnamed: LD72.2 (DOUT), LD73.4 (DIN)
unnamed: LD73.2 (DOUT), LD74.4 (DIN)
unnamed: LD74.2 (DOUT), LD75.4 (DIN)
unnamed: LD75.2 (DOUT), LD76.4 (DIN)
unnamed: LD76.2 (DOUT), LD77.4 (DIN)
unnamed: LD77.2 (DOUT), LD78.4 (DIN)
unnamed: LD78.2 (DOUT), LD79.4 (DIN)
unnamed: LD79.2 (DOUT), LD80.4 (DIN)
unnamed: LD80.2 (DOUT), LD81.4 (DIN)
unnamed: LD81.2 (DOUT), LD82.4 (DIN)
unnamed: LD82.2 (DOUT), LD83.4 (DIN)
unnamed: LD83.2 (DOUT), LD84.4 (DIN)
unnamed: LD84.2 (DOUT), LD85.4 (DIN)
unnamed: LD85.2 (DOUT), LD86.4 (DIN)
unnamed: LD86.2 (DOUT), LD87.4 (DIN)
unnamed: LD87.2 (DOUT), LD88.4 (DIN)
unnamed: LD88.2 (DOUT), LD89.4 (DIN)
unnamed: LD89.2 (DOUT), LD90.4 (DIN)
unnamed: LD90.2 (DOUT), LD91.4 (DIN)
unnamed: LD91.2 (DOUT), LD92.4 (DIN)
unnamed: LD92.2 (DOUT), LD93.4 (DIN)
unnamed: LD93.2 (DOUT), LD94.4 (DIN)
unnamed: LD94.2 (DOUT), LD95.4 (DIN)
unnamed: LD95.2 (DOUT), LD96.4 (DIN)
unnamed: LD96.2 (DOUT), LD97.4 (DIN)
unnamed: LD97.2 (DOUT), LD98.4 (DIN)
unnamed: LD98.2 (DOUT), LD99.4 (DIN)
unnamed: LD99.2 (DOUT), LD100.4 (DIN)
unnamed: LD100.2 (DOUT), LD101.4 (DIN)
unnamed: LD101.2 (DOUT), LD102.4 (DIN)
unnamed: LD102.2 (DOUT), LD103.4 (DIN)
unnamed: LD103.2 (DOUT), LD104.4 (DIN)
unnamed: LD104.2 (DOUT), LD105.4 (DIN)
unnamed: LD105.2 (DOUT), LD106.4 (DIN)
unnamed: LD106.2 (DOUT), LD107.4 (DIN)
unnamed: LD107.2 (DOUT), LD108.4 (DIN)
unnamed: LD108.2 (DOUT), LD109.4 (DIN)
unnamed: LD109.2 (DOUT), LD110.4 (DIN)
unnamed: LD110.2 (DOUT), LD111.4 (DIN)
unnamed: LD111.2 (DOUT), LD112.4 (DIN)
unnamed: LD112.2 (DOUT), LD113.4 (DIN)
unnamed: LD113.2 (DOUT), LD114.4 (DIN)
unnamed: LD114.2 (DOUT), LD115.4 (DIN)
unnamed: LD115.2 (DOUT), LD116.4 (DIN)
unnamed: LD116.2 (DOUT), LD117.4 (DIN)
unnamed: LD117.2 (DOUT), LD125.4 (DIN)
unnamed: LD118.4 (DIN), LD125.2 (DOUT)
unnamed: LD118.2 (DOUT), LD119.4 (DIN)
unnamed: LD119.2 (DOUT), LD124.4 (DIN)
unnamed: LD120.4 (DIN), LD124.2 (DOUT)
unnamed: LD120.2 (DOUT), LD121.4 (DIN)
unnamed: LD121.2 (DOUT), LD122.4 (DIN)
unnamed: LD32.2 (DOUT), LD123.4 (DIN)
unnamed: LD33.4 (DIN), LD123.2 (DOUT)
unnamed: D1.1 (A), MX000.2 (ROW)
unnamed: D1.2 (A), MX001.2 (ROW)
unnamed: D12.1 (A), MX002.2 (ROW)
unnamed: D12.2 (A), MX003.2 (ROW)
unnamed: D26.1 (A), MX004.2 (ROW)
unnamed: D26.2 (A), MX005.2 (ROW)
unnamed: D40.1 (A), MX006.2 (ROW)
unnamed: D40.2 (A), MX007.2 (ROW)
unnamed: D54.1 (A), MX008.2 (ROW)
unnamed: D54.2 (A), MX009.2 (ROW)
unnamed: D18.1 (A), MX10.2 (ROW)
unnamed: D18.2 (A), MX11.2 (ROW)
unnamed: D13.1 (A), MX012.2 (ROW)
unnamed: D13.2 (A), MX013.2 (ROW)
unnamed: D27.1 (A), MX014.2 (ROW)
unnamed: D27.2 (A), MX015.2 (ROW)
unnamed: D41.1 (A), MX016.2 (ROW)
unnamed: D41.2 (A), MX017.2 (ROW)
unnamed: D55.1 (A), MX018.2 (ROW)
unnamed: D55.2 (A), MX019.2 (ROW)
unnamed: D2.1 (A), MX020.2 (ROW)
unnamed: D2.2 (A), MX021.2 (ROW)
unnamed: D14.1 (A), MX022.2 (ROW)
unnamed: D14.2 (A), MX023.2 (ROW)
unnamed: D28.1 (A), MX024.2 (ROW)
unnamed: D28.2 (A), MX025.2 (ROW)
unnamed: D42.1 (A), MX026.2 (ROW)
unnamed: D42.2 (A), MX027.2 (ROW)
unnamed: D56.1 (A), MX028.2 (ROW)
unnamed: D56.2 (A), MX029.2 (ROW)
unnamed: D3.1 (A), MX030.2 (ROW)
unnamed: D3.2 (A), MX031.2 (ROW)
unnamed: D15.1 (A), MX032.2 (ROW)
unnamed: D15.2 (A), MX033.2 (ROW)
unnamed: D29.1 (A), MX034.2 (ROW)
unnamed: D29.2 (A), MX035.2 (ROW)
unnamed: D43.1 (A), MX036.2 (ROW)
unnamed: D43.2 (A), MX037.2 (ROW)
unnamed: D57.1 (A), MX038.2 (ROW)
unnamed: D57.2 (A), MX039.2 (ROW)
unnamed: D4.1 (A), MX040.2 (ROW)
unnamed: D4.2 (A), MX041.2 (ROW), MX041.125.2 (ROW)
unnamed: D16.1 (A), MX042.2 (ROW)
unnamed: D16.2 (A), MX043.2 (ROW)
unnamed: D30.1 (A), MX044.2 (ROW)
unnamed: D30.2 (A), MX045.2 (ROW)
unnamed: D44.1 (A), MX046.2 (ROW)
unnamed: D44.2 (A), MX047.2 (ROW)
unnamed: D58.1 (A), MX048.2 (ROW)
unnamed: D58.2 (A), MX049.2 (ROW)
unnamed: D5.1 (A), MX050.2 (ROW)
unnamed: D5.2 (A), MX051.2 (ROW)
unnamed: D17.1 (A), MX052.2 (ROW)
unnamed: D17.2 (A), MX053.2 (ROW)
unnamed: D31.1 (A), MX054.2 (ROW)
unnamed: D31.2 (A), MX055.2 (ROW)
unnamed: D45.1 (A), MX056.2 (ROW)
unnamed: D45.2 (A), MX057.2 (ROW)
unnamed: D59.1 (A), MX058.2 (ROW)
unnamed: D59.2 (A), MX059.2 (ROW)
unnamed: D6.1 (A), MX060.2 (ROW)
unnamed: D6.2 (A), MX061.2 (ROW)
unnamed: D32.1 (A), MX064.2 (ROW)
unnamed: D32.2 (A), MX065.2 (ROW)
unnamed: D46.1 (A), MX066.2 (ROW)
unnamed: D46.2 (A), MX067.2 (ROW)
unnamed: D60.1 (A), MX068.2 (ROW)
unnamed: D60.2 (A), MX069.2 (ROW)
unnamed: D19.1 (A), MX072.2 (ROW)
unnamed: D19.2 (A), MX073.2 (ROW)
unnamed: D33.1 (A), MX074.2 (ROW)
unnamed: D33.2 (A), MX075.2 (ROW)
unnamed: D47.1 (A), MX076.2 (ROW)
unnamed: D47.2 (A), MX077.2 (ROW)
unnamed: D61.1 (A), MX078.2 (ROW)
unnamed: D61.2 (A), MX079.2 (ROW)
unnamed: D20.1 (A), MX082.2 (ROW)
unnamed: D20.2 (A), MX083.2 (ROW)
unnamed: D34.1 (A), MX084.2 (ROW)
unnamed: D34.2 (A), MX085.2 (ROW)
unnamed: D48.1 (A), MX086.2 (ROW)
unnamed: D48.2 (A), MX087.2 (ROW)
unnamed: D62.1 (A), MX088.2 (ROW)
unnamed: D62.2 (A), MX089.2 (ROW)
unnamed: D7.1 (A), MX090.2 (ROW)
unnamed: D7.2 (A), MX091.2 (ROW)
unnamed: D21.1 (A), MX092.2 (ROW)
unnamed: D21.2 (A), MX093.2 (ROW)
unnamed: D35.1 (A), MX094.2 (ROW)
unnamed: D35.2 (A), MX095.2 (ROW)
unnamed: D49.1 (A), MX096.2 (ROW)
unnamed: D49.2 (A), MX097.2 (ROW)
unnamed: D63.1 (A), MX098.2 (ROW)
unnamed: D8.1 (A), MX100.2 (ROW)
unnamed: D8.2 (A), MX101.2 (ROW)
unnamed: D22.1 (A), MX102.2 (ROW)
unnamed: D22.2 (A), MX103.2 (ROW)
unnamed: D36.1 (A), MX104.2 (ROW)
unnamed: D36.2 (A), MX105.2 (ROW)
unnamed: D50.1 (A), MX106.2 (ROW)
unnamed: D50.2 (A), MX107.2 (ROW)
unnamed: D64.1 (A), MX108.2 (ROW)
unnamed: D64.2 (A), MX109.2 (ROW)
unnamed: D9.1 (A), MX110.2 (ROW)
unnamed: D9.2 (A), MX111.2 (ROW)
unnamed: D23.1 (A), MX112.2 (ROW)
unnamed: D23.2 (A), MX113.2 (ROW)
unnamed: D37.1 (A), MX114.2 (ROW)
unnamed: D37.2 (A), MX115.2 (ROW)
unnamed: D51.1 (A), MX116.2 (ROW)
unnamed: D51.2 (A), MX117.2 (ROW)
unnamed: D10.1 (A), MX120.2 (ROW)
unnamed: D24.1 (A), MX122.2 (ROW)
unnamed: D24.2 (A), MX123.2 (ROW)
unnamed: D38.1 (A), MX124.2 (ROW)
unnamed: D38.2 (A), MX125.2 (ROW)
unnamed: D52.1 (A), MX126.2 (ROW)
unnamed: D52.2 (A), MX127.175.2 (ROW)
unnamed: D11.1 (A), MX130.2 (ROW)
unnamed: D11.2 (A), MX131.2 (ROW)
unnamed: D25.1 (A), MX132.2 (ROW)
unnamed: D25.2 (A), MX133.2 (ROW)
unnamed: D39.1 (A), MX134.2 (ROW)
unnamed: D39.2 (A), MX135.2 (ROW)
unnamed: R4.2, TIP1.1 (B)
RGB_3v3: U1.6 (PA9), U2.2
RGB_5V: LD1.4 (DIN), U2.4
ROW0: D1.3 (K), D12.3 (K), D26.3 (K), D40.3 (K), D54.3 (K), U1.32 (PA6)
ROW1: D13.3 (K), D27.3 (K), D41.3 (K), D55.3 (K), U1.11 (PB3)
ROW2: D2.3 (K), D14.3 (K), D28.3 (K), D42.3 (K), D56.3 (K), U1.29 (PA3)
ROW3: D3.3 (K), D15.3 (K), D29.3 (K), D43.3 (K), D57.3 (K), U1.14 (PB6)
ROW4: D4.3 (K), D16.3 (K), D30.3 (K), D44.3 (K), D58.3 (K), U1.13 (PB5)
ROW5: D5.3 (K), D17.3 (K), D31.3 (K), D45.3 (K), D59.3 (K), U1.27 (PA1)
ROW6: D6.3 (K), D18.3 (K), D32.3 (K), D46.3 (K), D60.3 (K), U1.26 (PA0)
ROW7: D19.3 (K), D33.3 (K), D47.3 (K), D61.3 (K), U1.2 (PB13)
ROW8: D20.3 (K), D34.3 (K), D48.3 (K), D62.3 (K), U1.1 (PB12)
ROW9: D7.3 (K), D21.3 (K), D35.3 (K), D49.3 (K), D63.3 (K), U1.12 (PB4)
ROW10: D8.3 (K), D22.3 (K), D36.3 (K), D50.3 (K), D64.3 (K), U1.28 (PA2)
ROW11: D9.3 (K), D23.3 (K), D37.3 (K), D51.3 (K), U1.15 (PB7)
ROW12: D10.3 (K), D24.3 (K), D38.3 (K), D52.3 (K), U1.16 (PB8)
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
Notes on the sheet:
PA13 PA14

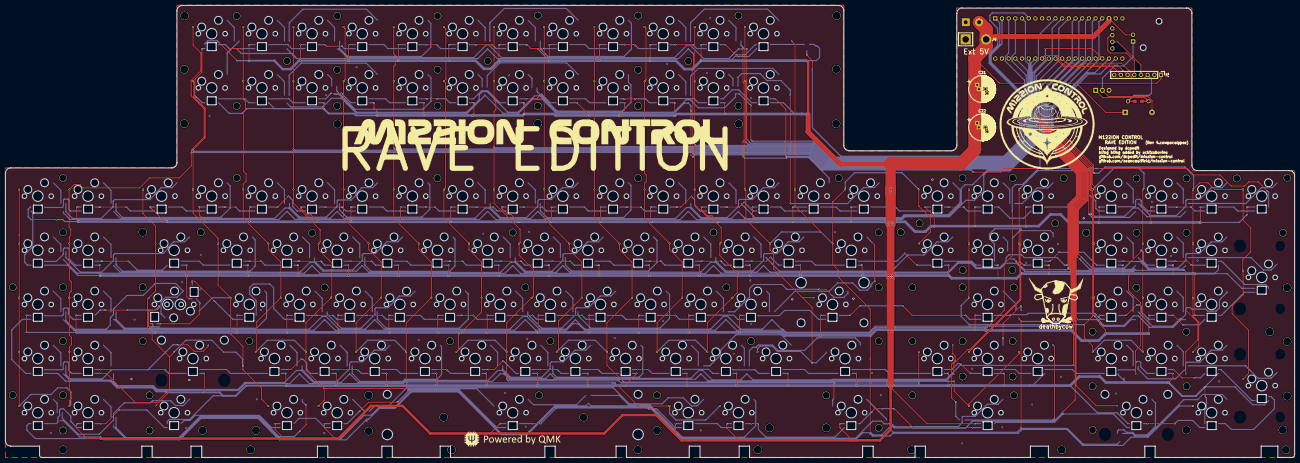
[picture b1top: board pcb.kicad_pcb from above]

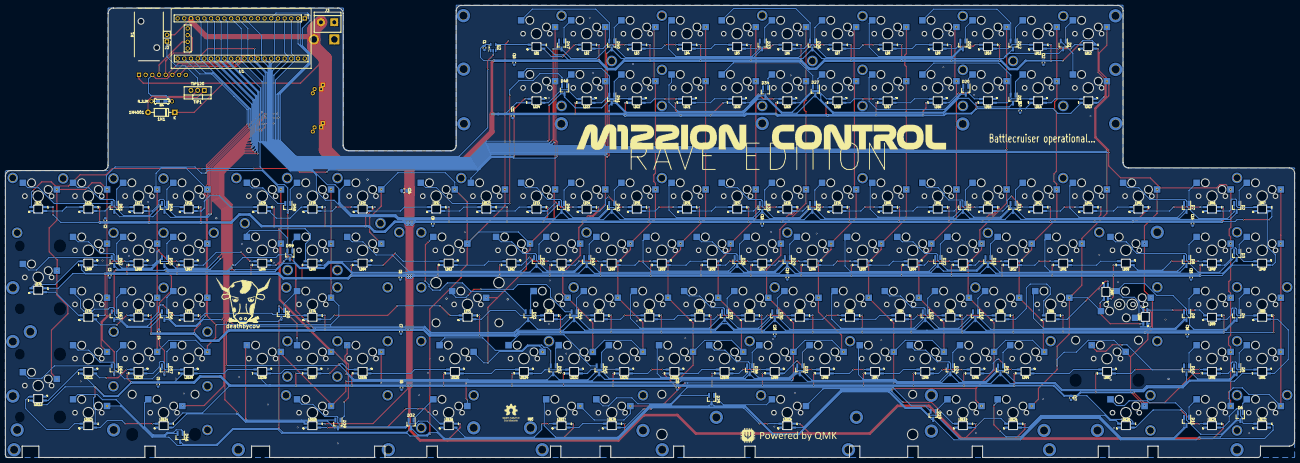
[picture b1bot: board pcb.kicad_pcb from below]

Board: 2 copper layers, 489.6 x 171.7 mm, 469 parts (213 on the bottom side), 283 nets.

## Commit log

2026-05-16 attempting to add RGB
2026-06-02 RGB added
2026-06-03 finished RGB
2026-06-03 add new FR4 plate files
2026-06-03 update README with new build info
2026-06-17 rev 4 with moved holes and caps
